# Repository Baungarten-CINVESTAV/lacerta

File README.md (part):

# Lacerta: Open Hardware Interface Engine for Embedded Systems

## Project Overview

**Lacerta** is an open-source hardware platform that enables the rapid creation of graphical interfaces for embedded systems using custom silicon.

**The whole documentation can be found** [**here**](https://baungarten-cinvestav.github.io/lacerta/).

The system allows developers to design graphical interfaces using a graphical configuration tool and deploy them directly to hardware implemented in a custom ASIC integrated with the Caravel SoC platform. The hardware renders the interface in real time and outputs the result to SPI-driven TFT/OLED screens commonly used in embedded devices.

The generated interface may include visual components such as:

- Buttons
- Horizontal and vertical bars
- Numeric indicators
- Status indicators

<p align="center">
<b>Figure 1.</b> Examples of graphical components supported by Lacerta, including buttons, horizontal and vertical bars, numeric indicators, graphics, and status indicators used to visualize real-time system data.
</p>

The ASIC receives information via UART streams and supports two main modes of operation for updating the display:

1. **Direct Mode:** Data received via UART is sent directly to the user project area. In this mode, the values are updated on the SPI TFT/OLED screen with minimal latency, ideal for simple or time-critical updates.

2. **Processing Mode:** Data from UART is first routed to the integrated RISC-V core, where any mathematical operations, functions, or custom logic can be applied. After processing, the results are sent to the user project area to update the display. This mode is suitable for applications requiring data manipulation or more complex interface logic.

This flexible architecture allows Lacerta to efficiently manage multiple inputs and screen objects using a single UART protocol, adapting to both straightforward and advanced use cases. Any other signal types must be converted to UART beforehand by external interface circuitry or preprocessing devices.

<p align="center">
<b>Figure 2.</b> Lacerta system concept: signals are processed by the Lacerta ASIC to generate the custom graphical HMI displayed on SPI-driven TFT/OLED displays for compact embedded installations.
</p>

# System Architecture Summary

The Lacerta platform is an open-source embedded graphics system built from four main parts: custom silicon, board-level hardware, firmware/control logic, and interface software. Together, these layers allow a host system to load graphics data, update interface objects, and drive a small SPI-connected display efficiently.

## Core architecture

Lacerta platform is a custom ASIC implemented in the **SKY130 process** and integrated inside the **Caravel user project area**. This subsystem realizes the hardware graphics engine that receives interface commands, updates the internal display state, and generates the output stream presented on the display.

The Lacerta ASIC follows a memory-centric architecture. Configuration data and runtime values enter the system through **UART**. Depending on the selected operating mode, the received data can be forwarded directly to the user project area or first processed by the embedded **Caravel RISC-V** processor. Internal transactions are routed through the **Wishbone interconnect** to the rendering logic, which updates the frame contents stored in memory. The display output block then reads that memory and continuously converts it into the signal required by the connected **SPI TFT/OLED display**.

The ASIC includes the following main modules:

- the external SRAM interface,
- the TFT SPI interface,
- the UART command interface,
- the Wishbone interface,
- the screen update logic,
- the drawing logic,
- and the shared memory subsystem.

<p align="center">
<b>Figure 3.</b> Block diagram of the Lacerta ASIC inside the Caravel environment. The figure shows how UART data and the embedded Caravel RISC-V processor interact through the Wishbone-connected control path, rendering logic, and memory subsystem; the updated frame data is then read by the display output block to drive the screen.
</p>

## Main subsystems

### Memory subsystem

The memory subsystem manages buffered access to external SRAM. It uses FIFOs, read/write buffering, and arbitration logic so several blocks can share memory safely without needing to handle low-level SRAM timing directly.

### Screen output subsystem

The screen path reads pixel data from memory and converts it into SPI transactions for the display. It supports TFT initialization, full or partial region refreshes, and a color lookup mechanism that maps compact pixel codes to RGB565 values. This reduces memory usage and makes repeated HMI colors efficient to store.

### Drawing subsystem

The drawing logic updates only the parts of the image that change. The `mask_generator` reads current pixel data, modifies selected regions based on object type, writes the result back to SRAM, and then triggers a refresh of the affected rectangle. This makes the system well suited for HMI elements such as bars, graphs, booleans, and segmented displays.

### Command and control subsystem

The control path is coordinated by `command_arbiter_decoder`, which receives transactions from UART and Wishbone interfaces and turns them into actions such as memory access, object redraws, screen refreshes, color-table updates, and reset/control operations.

### UART and Wishbone interfaces

UART provides an external host-facing command port for loading assets, configuring the display, and triggering updates. Wishbone provides processor-oriented access to both control registers and shared memory, allowing the embedded Caravel processor or another SoC master to work with the same graphics system.

## Typical operation

In normal use, a host first loads graphics assets or configuration data into SRAM. The display is initialized, then object updates are triggered through UART or processor commands. The drawing engine modifies only the required image region in memory, and the screen subsystem refreshes only that changed rectangle on the TFT. This avoids full-screen redraws and improves efficiency for dynamic interfaces.

## Lacerta board role

The Lacerta Board packages the SoC with the supporting hardware needed for practical use, including power regulation, clocking, USB-to-serial connectivity, SPI Flash support, GPIO access, and display/peripheral connections. It serves as the physical platform for development, testing, and demonstration of the Lacerta graphics architecture.

# System Development

The development of the Lacerta platform spans the complete hardware and software realization flow, from digital design and verification to physical implementation and system-level integration. This section describes the main stages used to transform the Lacerta concept into a functional platform, including RTL design, verification, layout generation, gate-level validation, PCB development, and the creation of the interface design software.

Together, these activities define the engineering workflow followed to implement, test, and deploy Lacerta as an open-source embedded graphical interface system. Each subsection highlights a different part of this process and explains how the individual development tasks contribute to the final platform.

## Lacerta RTL

**RTL code can be found** [**here**](https://github.com/Baungarten-CINVESTAV/lacerta/tree/main/verilog/rtl).

### System Purpose

The system is designed to display graphical HMI content on a TFT screen and to update only the screen regions that change.

At a functional level, the system must:

- receive commands and image-related data,
- store image bytes and mask bytes in external SRAM,
- modify selected objects inside the stored image,
- fetch the corresponding pixel data,
- convert logical pixel information into display colors,
- and transmit the final bytes to the TFT controller.

The design is organized around a shared memory architecture. Instead of each module touching the SRAM directly, all active clients use a common memory subsystem with buffered read and write channels, as shown in the figure below.

### High-Level Functional Flow

The complete display flow is:

1. A host or processor sends control commands or image data.
2. The command path decodes the request and either:
   - writes data into the shared memory system,
   - updates display-related configuration,
   - or starts a drawing operation.
3. The memory subsystem transfers bytes between internal buffers and external SRAM.
4. If an HMI object changes, `mask_generator` reads the corresponding image region, updates the stored bytes, and writes the modified data back into SRAM.
5. Once the image region is ready, `screen_system` requests the affected window from memory.
6. `tft_control_fsm` streams TFT commands and pixel bytes through `spi_master`.
7. The TFT receives only the updated region instead of a full-screen redraw.

This makes the system well suited for dashboards, indicators, bars, graphs, and symbolic objects that change frequently in small areas.

### Top-Level Integration (User Project Wrapper)

#### `dig_top.v` 

`dig_top` is the main integration point of the RTL system.
It connects:
- the UART interface,
- the Wishbone interface,
- the external SRAM,
- the TFT SPI pins,
- the shared memory subsystem,
- the drawing engine,
- and the display engine.
Its main functional job is to route requests from several clients into the memory system and to coordinate which subsystem is producing or consuming pixel data.

The clients connected to the shared memory system are:

- UART host write path,
- UART host read path,
- screen-system read path,
- drawing-engine read path,
- drawing-engine write path,
- Wishbone memory read path,
- Wishbone memory write path.

Inside `dig_top`, each client is assigned to a dedicated buffer slot. The top-level combinational logic packs the individual requests into the vectors expected by `mem_sys`.

`dig_top` also derives the frame-update rectangle used by the display block:

- `frame_st_x`
- `frame_end_x`
- `frame_width`
- `frame_st_y`
- `frame_end_y`
- `frame_height`
- `frame_st_pix`

These values are taken from the drawing object parameters so that, after a drawing operation, the correct screen region can be refreshed automatically.

Another important top-level task is Wishbone routing. `dig_top` chooses whether a Wishbone transaction goes to:

- `wb_slave_memory_mapped` for control/MMIO accesses,
- or `wb_slave_to_mem_sys_ports` for direct SRAM-backed data accesses.

### End-to-End Operation Examples

#### Example 1: Loading image data from UART

1. The host sends UART packets.
2. `uart_ip_memory_mapped` converts them into internal writes.
3. `command_arbiter_decoder` interprets those writes as host memory-transfer commands.
4. The host write buffer receives the data bytes.
5. `mem_sys` schedules the write burst.
6. `buffers_discharger` sends the bytes to SRAM through `sram_controller`.

#### Example 2: Updating an HMI object

1. The host or processor writes object parameters.
2. `command_arbiter_decoder` stores width, height, position, object value, and memory addresses.
3. A start command asserts `drw_inc_start`.
4. `mask_generator` begins a read-modify-write sequence.
5. The old bytes are fetched from SRAM through `mem_sys`.
6. The updated bytes are written back to SRAM through `mem_sys`.
7. `mask_generator` asserts `ss_start`.
8. `screen_system` refreshes the affected rectangle on the TFT.

#### Example 3: Refreshing the sidebar

1. A control write asserts `ss_ld_sidebar`.
2. `tft_control_fsm` programs the sidebar coordinates into the TFT.
3. It requests the corresponding SRAM burst.
4. Two bytes per pixel are read.
5. Those bytes are transmitted directly through `spi_master`.

### Main Functional Role of Each Major Module

- `dig_top`: integrates the whole system and routes all subsystem interfaces.
- `command_arbiter_decoder`: converts UART/Wishbone commands into internal control actions.
- `uart_ip_memory_mapped`: converts UART packets into internal memory-mapped transactions.
- `wb_slave_memory_mapped`: converts Wishbone MMIO accesses into control transactions.
- `wb_slave_to_mem_sys_ports`: converts Wishbone data accesses into shared-memory bursts.
- `mem_sys`: arbitrates shared access to external SRAM.
- `buffers`: stores temporary read and write data for all clients.
- `buffers_filler`: fills read buffers from SRAM.
- `buffers_discharger`: empties write buffers into SRAM.
- `sram_controller`: drives the physical SRAM pins.
- `mask_generator`: updates image regions according to HMI object logic.
- `screen_system`: top display block for TFT output.
- `tft_control_fsm`: performs TFT initialization and region-based pixel transfer.
- `color_mapping_table`: converts compact pixel codes into RGB565 colors.
- `spi_master`: serializes commands and pixel bytes onto the TFT SPI bus.

## Lacerta Verification

**Verilog TB code can be found** [**here**](https://github.com/Baungarten-CINVESTAV/lacerta/tree/main/verilog/dv/lacerta).

A layered verification strategy was used to validate Lacerta from block level up to full-system behavior. The intent was not only to prove that individual modules operate correctly in isolation, but also to verify that the complete command, memory, drawing, and display paths remain coherent when exercised through the same interfaces used in deployment.

At the block level, dedicated environments were created for the UART front end, the shared memory subsystem, the Wishbone adapters, the command decoder, and the display-related logic. These environments focused on local protocol correctness, handshake legality, data stability, and forward progress. The later sections of this document list the principal checks captured for each block.

At the system level, the main integration environment is `verif/dig_top_tb.sv`. This testbench drives the top-level `dig_top` instance through the UART path, connects the design to an SRAM behavioral model (`CY7C1049GN_i`), and observes the TFT SPI outputs exactly as a real deployment would use them. In practice, this makes the testbench an end-to-end verification vehicle: a command is injected as UART traffic, decoded by the control plane, executed through the memory subsystem, and finally checked either at the SRAM image or at the TFT serial output.

<p align="center">
<b>Figure 4.</b> The diagram summarizes the main verification components, including the clock and reset infrastructure, golden reference data, stimulus path, UART bus functional model, SRAM model, and checker logic used to validate the DUT behavior during gate-level simulation.
</p>

More information about the simulation flow, active checkers, and expected data paths can be found in [dig_top_tb_flow_diagram.html](dig_top_tb_flow_diagram.html).

### System-Level Verification

The full-system verification flow is organized around three complementary ideas:

1. **Interface-faithful stimulus**  
   The testbench does not force deep internal signals to mimic system behavior. Instead, it uses the UART Bus Functional Model (`uart_bfm`) and the helper task `uart_write_mem()` to generate valid command packets byte by byte. This ensures that the UART receive path, packet decoder, command arbiter, and downstream blocks are exercised together.

2. **Independent reference data**  
   The testbench builds its own expected data structures before execution begins:
    `tft_init_mem` stores the expected TFT initialization sequence, including command, data, and delay entries.
    `tft_sidebar` stores the expected sidebar stream sent to the TFT.
    `tft_active_area` stores the logical active-screen image used for full-frame display verification.
    `tb_sram` acts as a golden SRAM image. It is initialized from the active-area data and then updated by the testbench's own object-drawing rules before being compared against the DUT-visible SRAM model.

3. **Concurrent checking**  
   Verification is not deferred to a single final comparison. The testbench runs several checker threads in parallel, so protocol violations, timing mismatches, stream ordering errors, and memory corruption are detected close to the cycle where they occur. This is especially important for gate-level simulation, where failures may arise from control sequencing or handshake timing rather than purely functional logic.

### `dig_top_tb.sv` Verification Flow

The top-level testbench starts from a simple but realistic infrastructure:

- a 50 MHz clock generated with `always #10ns clk = !clk;`,
- an active-low reset released after 40 ns,
- an SRAM behavioral model connected to the external-memory pins,
- UART-driven stimulus,
- a serial-output checker for the TFT SPI path,
- and a 30-second timeout thread to convert deadlock into an explicit failure.

After reset, the system verification scenario progresses through the following phases.

#### 1. TFT initialization memory programming

The testbench writes every entry of `tft_init_mem` through UART to the control address used by the screen subsystem. This stage verifies that Lacerta accepts configuration traffic through the host path and correctly stores screen-initialization data before any display action is requested.

#### 2. TFT initialization sequence execution

Once the initialization table is loaded, the testbench configures the SPI clock divider and triggers screen initialization. A dedicated checker thread waits until the TFT control FSM enters its initialization state and then validates each emitted entry:

- for command/data entries, the checker compares `{rom_type, tnsm_data}` against the expected `tft_init_mem` content;
- for delay entries, it measures the elapsed clock cycles and confirms that the observed delay is at least the programmed number of milliseconds multiplied by `CLK_CYCLES_PER_MS`.

This stage verifies more than register programming. It checks that the initialization ROM is consumed in the correct order, that delay entries are honored in time, and that the SPI path receives the exact bytes expected by the TFT controller. After the sequence completes, the testbench asserts that `initialization_done` is high.

#### 3. Sidebar transfer verification

The testbench then prepares a burst write into the shared memory system and streams the sidebar payload through repeated UART writes. After the sidebar-load command is issued, the testbench checks both control behavior and output behavior:

- `sidebar_ongoing` must assert after the command and later deassert when the transfer completes;
- the read buffer must be empty and the read-page generator must be idle at the end of the operation;
- every SPI byte transmitted during the sidebar update must match the expected `tft_sidebar` sequence;
- the `tft_dc` line must indicate command bytes for `CASET`, `RASET`, and `RAMWR`, and data bytes everywhere else.

This verifies the complete path from host programming, to SRAM write buffering, to screen-system memory fetch, to TFT serialization.

#### 4. Color-mapping table programming

The testbench writes randomized RGB565 values into every color-map entry and then reads the corresponding internal table state after a short propagation delay. This confirms that compact logical pixel codes used in the screen image are translated through the correct table entries before being sent to the TFT interface.

#### 5. Full active-screen fetch and display

To verify full-image display behavior, the testbench first loads the active-screen image into SRAM through the UART-controlled write path. It then programs object geometry fields so the screen subsystem fetches the entire active display region and emits it over SPI.

During this phase, the verification logic checks:

- that the TFT control FSM asserts `busy` after the fetch request and later returns to idle;
- that the read buffer is empty and the page generator is no longer busy after completion;
- that the command/window bytes (`CASET`, `RASET`, `RAMWR`, and coordinate bytes) match the expected `tft_active_area` header;
- that each logical pixel in `tft_active_area` is converted into the correct two-byte RGB565 value using the live `color_map` table;
- and that the command/data framing on `tft_dc` remains correct during the whole transfer.

This is an important system-level check because it validates the interaction among stored pixel data, color expansion, frame-window generation, TFT command sequencing, and SPI serialization.

#### 6. Constrained-random drawing-object verification

After the static display paths are verified, the testbench executes `TB_NUM_OBJECTS` randomized drawing scenarios. For each iteration it selects:

- an object type,
- object width and height,
- a value parameter,
- a legal start position (`st_x`, `st_y`),
- and, for mask objects, a legal mask-source base address.

The object type rotates through the drawing modes implemented in the testbench tasks:

- `draw_horizontal_type()`
- `draw_vertical_type()`
- `draw_graph_type()`
- `draw_mask_type()`

Each task programs the DUT through UART exactly as software would: it writes object type, dimensions, start address, screen coordinates, and trigger/value fields. The testbench then waits for the drawing engine completion handshake (`MASK_GEN_PATH.done`) and updates the shadow image `tb_sram` according to an independent expected-behavior model:

- **Horizontal object:** the MSB of each target pixel is set according to the horizontal position relative to `obj_value`.
- **Vertical object:** the MSB of each target pixel is set according to the vertical position relative to `obj_value`.
- **Graph object:** the existing region is shifted and a new column is inserted, modeling graph-history behavior rather than a simple overwrite.
- **Mask object:** the update uses a second memory region as the mask source, stressing source/destination addressing interactions.

After every object operation, `check_sram_consistency()` compares the golden `tb_sram` contents against the actual external SRAM model seen by the DUT. This immediate comparison is valuable because it localizes failures to the most recent object operation instead of postponing diagnosis to the end of the simulation.

#### 7. Microprocessor-enable handoff

At the end of the scenario, the testbench issues the UART command that enables the embedded microprocessor path and verifies that `up_enable` is asserted. This closes the loop on one more top-level control action and ensures the system can hand control to the processor-side flow after host-side configuration.

### Active Checker Structure

The `dig_top_tb.sv` environment contains several simultaneously active verification mechanisms:

- **TFT initialization checker:** validates initialization bytes and delay lengths.
- **Sidebar stream checker:** validates TFT payload bytes and command/data framing.
- **Active-area stream checker:** validates frame-window commands and RGB565-expanded pixel output.
- **SRAM shadow-model checker:** compares the expected image memory against the SRAM model after each draw operation.
- **SPI serialization checker:** samples `tft_mosi` on `tft_sck` edges and confirms that every acknowledged `tnsm_data` byte is serialized MSB first.
- **Control/status assertions:** check flags such as `initialization_done`, `sidebar_ongoing`, `busy`, buffer-empty conditions, and `up_enable`.
- **Timeout protection:** terminates the simulation with a fatal error if the full scenario fails to make progress within 30 seconds.

Together, these checkers provide both transaction-level and bit-level confidence. A failure can therefore be caught as a bad control transition, a wrong memory update, an incorrect TFT byte, or even a serialization mismatch on the SPI output pin.

### Relation to GLS and Documentation Artifacts

This same end-to-end style is especially useful for gate-level simulation because it exercises long control sequences, back-pressure conditions, and external-interface timing without simplifying the problem to a purely combinational comparison. More detailed information about the simulation flow, active checkers, and expected data paths can be found in [dig_top_tb_flow_diagram.html](dig_top_tb_flow_diagram.html). That file documents the actual structure implemented in `dig_top_tb.sv`: UART-driven initialization, sidebar transfer, color-map programming, full active-area fetch, constrained-random object drawing with per-object SRAM comparison, and final processor enable.

Overall, the Lacerta verification methodology combines block-level protocol checking, system-level end-to-end stimulus, reference-model comparison, and gate-level observability. This gives strong confidence that the platform is not only logically correct, but also integration-ready across its communication, memory, drawing, and display subsystems.

### WB Slave to Memory Mapped

The verification plan for the **WB Slave to Memory Mapped** block focuses on protocol correctness, proper memory-side control generation, and legal read/write handshaking.

1. Verify that the Wishbone slave acknowledges only when a valid master request is active.
2. Verify that an active Wishbone request is acknowledged within the maximum allowed number of clock cycles.
3. Verify that `wb_ack_o` is asserted for only one clock cycle per transaction.
4. Verify that address, data, and control signals remain stable while a request is active and has not yet been acknowledged.
5. Verify that `mem_we` is asserted, and `mem_re` is not asserted, during Wishbone write requests.
6. Verify that `mem_re` is asserted, and `mem_we` is not asserted, during Wishbone read requests.
7. Verify that `wb_cyc_i` and `wb_stb_i` are deasserted only after `wb_ack_o`, preventing overlapping requests.
8. Verify that `mem_waddr`, `mem_wdata`, and `mem_wmask` correctly reflect the Wishbone address, data, and byte-select signals during write requests.
9. Verify that `mem_raddr` correctly reflects the Wishbone address during read requests.
10. Verify that `wb_dat_o` returns the same data received from memory when a Wishbone read request completes.
11. Verify that `mem_wr_data_ack` can be asserted only while a Wishbone write transaction is in progress.
12. Verify that `mem_rdy` can be asserted only while a Wishbone read transaction is in progress.

### WB Slave to Read/Write Ports

The verification plan for the **WB Slave to Read/Write Ports** block checks correct Wishbone behavior, proper coordination with the memory-system ports, and correct sequencing of read and write transactions initiated by the microprocessor side.

1. Verify that the Wishbone slave acknowledges only when a valid master request is active.
2. Verify that `wb_ack_o` is asserted for only one clock cycle per transaction.
3. Verify that address, data, and control signals remain stable while a request is active and has not yet been acknowledged.
4. Verify that `wpg_busy` is asserted only for Wishbone write requests and remains clear for read requests.
5. Verify that `wpg_busy` remains asserted until `wpg_ack` is received.
6. Verify that `rpg_busy` is asserted only for Wishbone read requests and remains clear for write requests.
7. Verify that `rpg_busy` remains asserted until `rpg_ack` is received.
8. Verify that `wb_cyc_i` and `wb_stb_i` are deasserted only after `wb_ack_o`, preventing overlapping requests.
9. Verify that `up_en` does not change while a read or write process is in progress.
10. Verify that `up_soft_reset` does not change while a read or write process is in progress.
11. Verify that `wpg_st_addr`, `wpg_burst_length`, and `wr_buff_wdata` are correctly loaded during Wishbone write requests.
12. Verify that `wpg_st_addr`, `wpg_burst_length`, and `wr_buff_wdata` remain stable until `wpg_ack` is asserted.
13. Verify that `rpg_st_addr` and `rpg_burst_length` are correctly loaded during Wishbone read requests.
14. Verify that `rpg_st_addr` and `rpg_burst_length` remain stable until `rpg_ack` is asserted.
15. Verify that `wr_buff_wren` is asserted only during Wishbone write requests and only once per write transaction.
16. Verify that `rd_buff_rden` is asserted only during Wishbone read requests and exactly `NUM_ACCESSES` times per read transaction.
17. Verify that `rpg_ack` can be asserted only while a master read operation is ongoing.
18. Verify that `wpg_ack` can be asserted only while a master write operation is ongoing.
19. Verify that a Wishbone read transaction completes when `rpg_ack` is asserted.
20. Verify that a Wishbone write transaction completes when `wpg_ack` is asserted.
21. Verify that the read buffer is empty whenever no Wishbone read operation is in progress.
22. Verify that the data returned at the end of a Wishbone read matches the data delivered by the memory system.
23. Verify that Wishbone read and write transactions can start only when the microprocessor interface is enabled and not in soft reset.

### Command Arbiter Decoder

The verification plan for the **Command Arbiter Decoder** block checks the validity of drawing commands, busy-state behavior, and the control rules used when enabling or resetting the memory-access path.

1. Verify that when `drw_inc_start` is asserted, the drawing object type is within the valid range and both object width and object height are greater than `MIN_OBJECT_WIDTH_HEIGHT`.
2. Verify that asserting `drw_inc_start` causes `drw_inc_busy` to transition from `0` to `1`.
3. Verify that the drawing data sent to the rendering circuit remains stable while `drw_inc_busy` is asserted.
4. Verify that `drw_inc_busy` is not asserted for longer than `DRW_BUSY_TIMEOUT` clock cycles.
5. Verify that `wb_slave_up_en` is asserted when the UART write command address is `18`.
6. Verify that `wb_slave_up_en` can be deasserted only when no memory-system access transaction is in progress.
7. Verify that `up_soft_reset` can be asserted only when no memory-system access transaction is in progress.

### Mask Generator

The verification plan for the **Mask Generator** block validates correct start/busy sequencing and ensures that internal read/write activity occurs only while the block is actively processing a drawing operation.

1. Verify that asserting `start` causes `busy` to transition from `0` to `1`.
2. Verify that `start` cannot be asserted while `busy` or `done` is already asserted.
3. Verify that when `busy` is deasserted, `rpg_busy` and `wpg_busy` are both low and `rd_buff_empty` is high.
4. Verify that `rd_buff_rden` cannot be asserted when `rd_buff_empty` is high.
5. Verify that `wr_buff_wren` cannot be asserted when `wr_buff_full` is high.
6. Verify that `rpg_busy`, `wpg_busy`, `rpg_ack`, `wpg_ack`, `wr_buff_full`, `rd_buff_rden`, and `wr_buff_wren` can be asserted only while `busy` is high.

## Lacerta RTL Verification

**Verilog TB code can be found** [**here**](https://github.com/Baungarten-CINVESTAV/lacerta/tree/main/verilog/dv/lacerta).

The RTL simulation stage was used to verify the functional behavior of the Lacerta top-level design and to confirm the correctness of the TFT initialization transaction sequence before physical implementation. In this test, the simulation output shows that the expected delays were observed and that the initialization values stored in `tft_init_mem` were transmitted correctly to `spi_master`. The resulting log provides evidence that the initialization FSM and SPI output path behave as intended during the early display bring-up sequence at the RTL verification stage.

A section from the RTL simulation log is shown below. The complete log file is available for download here: [lacerta_gate_level_simulation.log](documentation_mkdoc/docs/lacerta_gate_level_simulation.log).

```text
Time resolution is 1 ps
open_wave_config /home/miguel/Documents/lacerta/verif/work/work.dig_top_tb.wcfg
run -all
delay encountered 20
PASS: correct delay 1020321 for entry 0 was measured
delay encountered 120
PASS: correct delay 6049997 for entry 1 was measured
PASS: correct tft_init_mem data 0001 for entry 2 was sent to spi_master
delay encountered 150
PASS: correct delay 7549959 for entry 3 was measured
PASS: correct tft_init_mem data 0011 for entry 4 was sent to spi_master
delay encountered 120
PASS: correct delay 6049959 for entry 5 was measured
PASS: correct tft_init_mem data 003a for entry 6 was sent to spi_master
PASS: correct tft_init_mem data 0155 for entry 7 was sent to spi_master
delay encountered 10
PASS: correct delay 549920 for entry 8 was measured
PASS: correct tft_init_mem data 0036 for entry 9 was sent to spi_master
PASS: correct tft_init_mem data 01a8 for entry 10 was sent to spi_master
PASS: correct tft_init_mem data 002a for entry 11 was sent to spi_master
PASS: correct tft_init_mem data 0100 for entry 12 was sent to spi_master
PASS: correct tft_init_mem data 0100 for entry 13 was sent to spi_master
PASS: correct tft_init_mem data 0101 for entry 14 was sent to spi_master
PASS: correct tft_init_mem data 013f for entry 15 was sent to spi_master
PASS: correct tft_init_mem data 002b for entry 16 was sent to spi_master
PASS: correct tft_init_mem data 0100 for entry 17 was sent to spi_master
PASS: correct tft_init_mem data 0100 for entry 18 was sent to spi_master
PASS: correct tft_init_mem data 0100 for entry 19 was sent to spi_master
PASS: correct tft_init_mem data 01ef for entry 20 was sent to spi_master
PASS: correct tft_init_mem data 0020 for entry 21 was sent to spi_master
PASS: correct tft_init_mem data 0013 for entry 22 was sent to spi_master
```

### RTL/GL simulation

A custom script was developed to execute RTL and GL simulations with the Caravel infrastructure, as the default Caravel simulation flow was out of date and only supported cocotb-based testbenches. This approach was necessary to correctly run assertion-based testbenches and ensure compatibility with the current Lacerta verification environment, which relies on SystemVerilog assertions and traditional testbench flows.

The custom script, located in the [`dv_setup`](dv_setup) directory (`lacerta/dv_setup`), automates the setup and execution of both RTL and gate-level (GL) simulations. It handles environment configuration, Makefile patching, and the selection of the appropriate simulation mode (`SIM_MODE=RTL` or `SIM_MODE=GL`). The script also allows users to select which DV test to run via the `DV_TEST` variable, making it flexible for different verification scenarios.

This approach ensures that all assertions and checkers in the testbenches are properly evaluated during simulation, which is not possible with the default Caravel cocotb-only flow. The script supports both host-based and Docker-based simulation environments, making it suitable for a variety of development setups.

The main testbench (`lacerta_tb.sv`) and its associated waveform files can be found in the `lacerta/verilog/dv/lacerta` folder. The following figure shows an example waveform generated during simulation:

<p align="center">
<b>Figure 6.</b> Example simulation waveform from the Lacerta RTL testbench, illustrating the verification an initial configuration of the memory_system through UART using IO port 5 an 6.
</p>

For detailed instructions on how to use the RTL/GL simulation flow, refer to the documentation and scripts in

## Hardening Configuration

**Librelane configuration can be found** [**here**](https://github.com/Baungarten-CINVESTAV/lacerta/tree/main/openlane/user_project_wrapper).

This page documents the OpenLane hardening setup used for the `user_project_wrapper` flow in Lacerta and records the top-level hardening option selected for the project.

### Selected Hardening Option

The selected hardening option is:

**Flat on Top-Level (Single Flat Design)**

In this approach, the full user project is hardened directly at the `user_project_wrapper` level. OpenLane reads the top-level wrapper together with the project RTL and generates a single physical implementation for the wrapper.

This option is typically used when:

- the goal is to optimize the complete design as one integrated block,
- higher top-level performance is preferred over separate block-level optimization,
- and global placement and routing decisions are acceptable across the full design.

For this flow, the top-level OpenLane run is performed inside:

`openlane/user_project_wrapper`

### Single OpenLane Run Setup

For a flat top-level hardening flow, the wrapper configuration should:

- set `DESIGN_IS_CORE` to `1` when required by the selected OpenLane flow,
- include `user_project_wrapper.v` together with the full user RTL in `VERILOG_FILES`,
- and ensure that `user_project_wrapper.v` directly instantiates the project design.

In Lacerta, the wrapper configuration includes the top-level RTL together with the main functional blocks such as:

- `dig_top.v`
- `command_arbiter_decoder.v`
- UART modules
- Wishbone slave modules
- screen control modules
- drawing modules
- memory-system RTL

### Current Wrapper Configuration

The wrapper hardening file is:

`openlane/user_project_wrapper/config.json`

This configuration includes the full RTL list under `VERILOG_FILES`, which matches the flat top-level hardening strategy. The file also enables several implementation and signoff-related options for a full wrapper run.

Key settings from `config.json`:

```json
"SYNTH_ELABORATE_ONLY": false,
"RUN_POST_GPL_DESIGN_REPAIR": true,
"RUN_POST_CTS_RESIZER_TIMING": true,
"DESIGN_REPAIR_BUFFER_INPUT_PORTS": true,
"FP_PDN_ENABLE_RAILS": true,
"RUN_ANTENNA_REPAIR": true,
"RUN_FILL_INSERTION": true,
"RUN_TAP_ENDCAP_INSERTION": true,
"RUN_CTS": true,
"RUN_IRDROP_REPORT": true
```

Additional implementation-oriented settings used in the same file include:

```json
"SYNTH_STRATEGY": "DELAY 4",
"FP_CORE_UTIL": 30,
"DESIGN_REPAIR_REMOVE_BUFFERS": true,
"DESIGN_REPAIR_MAX_CAP_PCT": 85,
"DESIGN_REPAIR_MAX_SLEW_PCT": 85,
"RUN_POST_GRT_DESIGN_REPAIR": true,
"RUN_POST_GRT_RESIZER_TIMING": true,
"PL_RESIZER_HOLD_SLACK_MARGIN": 0.3,
"GRT_RESIZER_HOLD_SLACK_MARGIN": 0.3
```

### Reference Hardening Variables for Top-Level Integration

The following variables were identified as the hardening option reference for top-level integration:

```json
"QUIT_ON_SYNTH_CHECKS": 1,
"FP_PDN_CHECK_NODES": 1,
"SYNTH_ELABORATE_ONLY": 0,
"PL_RANDOM_GLB_PLACEMENT": 0,
"PL_RESIZER_DESIGN_OPTIMIZATIONS": 1,
"PL_RESIZER_TIMING_OPTIMIZATIONS": 1,
"GLB_RESIZER_DESIGN_OPTIMIZATIONS": 1,
"GLB_RESIZER_TIMING_OPTIMIZATIONS": 1,
"PL_RESIZER_BUFFER_INPUT_PORTS": 1,
"FP_PDN_ENABLE_RAILS": 1,
"GRT_REPAIR_ANTENNAS": 1,
"RUN_FILL_INSERTION": 1,
"RUN_TAP_DECAP_INSERTION": 1,
"RUN_CTS": 1,
"RUN_CVC": 1
```

These settings describe the intended behavior of a robust full-wrapper hardening run, including synthesis checking, placement control, timing optimization, PDN generation, antenna repair, filler insertion, tap/decap insertion, clock-tree synthesis, and final electrical checks.

<p align="center">
<b>Figure 5.</b> KLayout view of the Lacerta custom ASIC layout, showing the physical implementation of the design within the SKY130 Caravel user project area.
</p>

To complement the layout view, Table 1 summarizes the main implementation metrics of the Lacerta chip extracted from the final OpenLane hardening results. These values provide a compact overview of the physical size, logic complexity, utilization, power, timing, and routing quality achieved for the final ASIC integration.

| Parameter                        | Value                        |
|-----------------------------------|------------------------------|
| Technology / integration platform | SKY130 in Caravel user project area |
| Die size                         | 2920 um x 3520 um            |
| Die area                         | 10.2784 mm²                  |
| Core size                        | 2908.58 um x 3497.92 um      |
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
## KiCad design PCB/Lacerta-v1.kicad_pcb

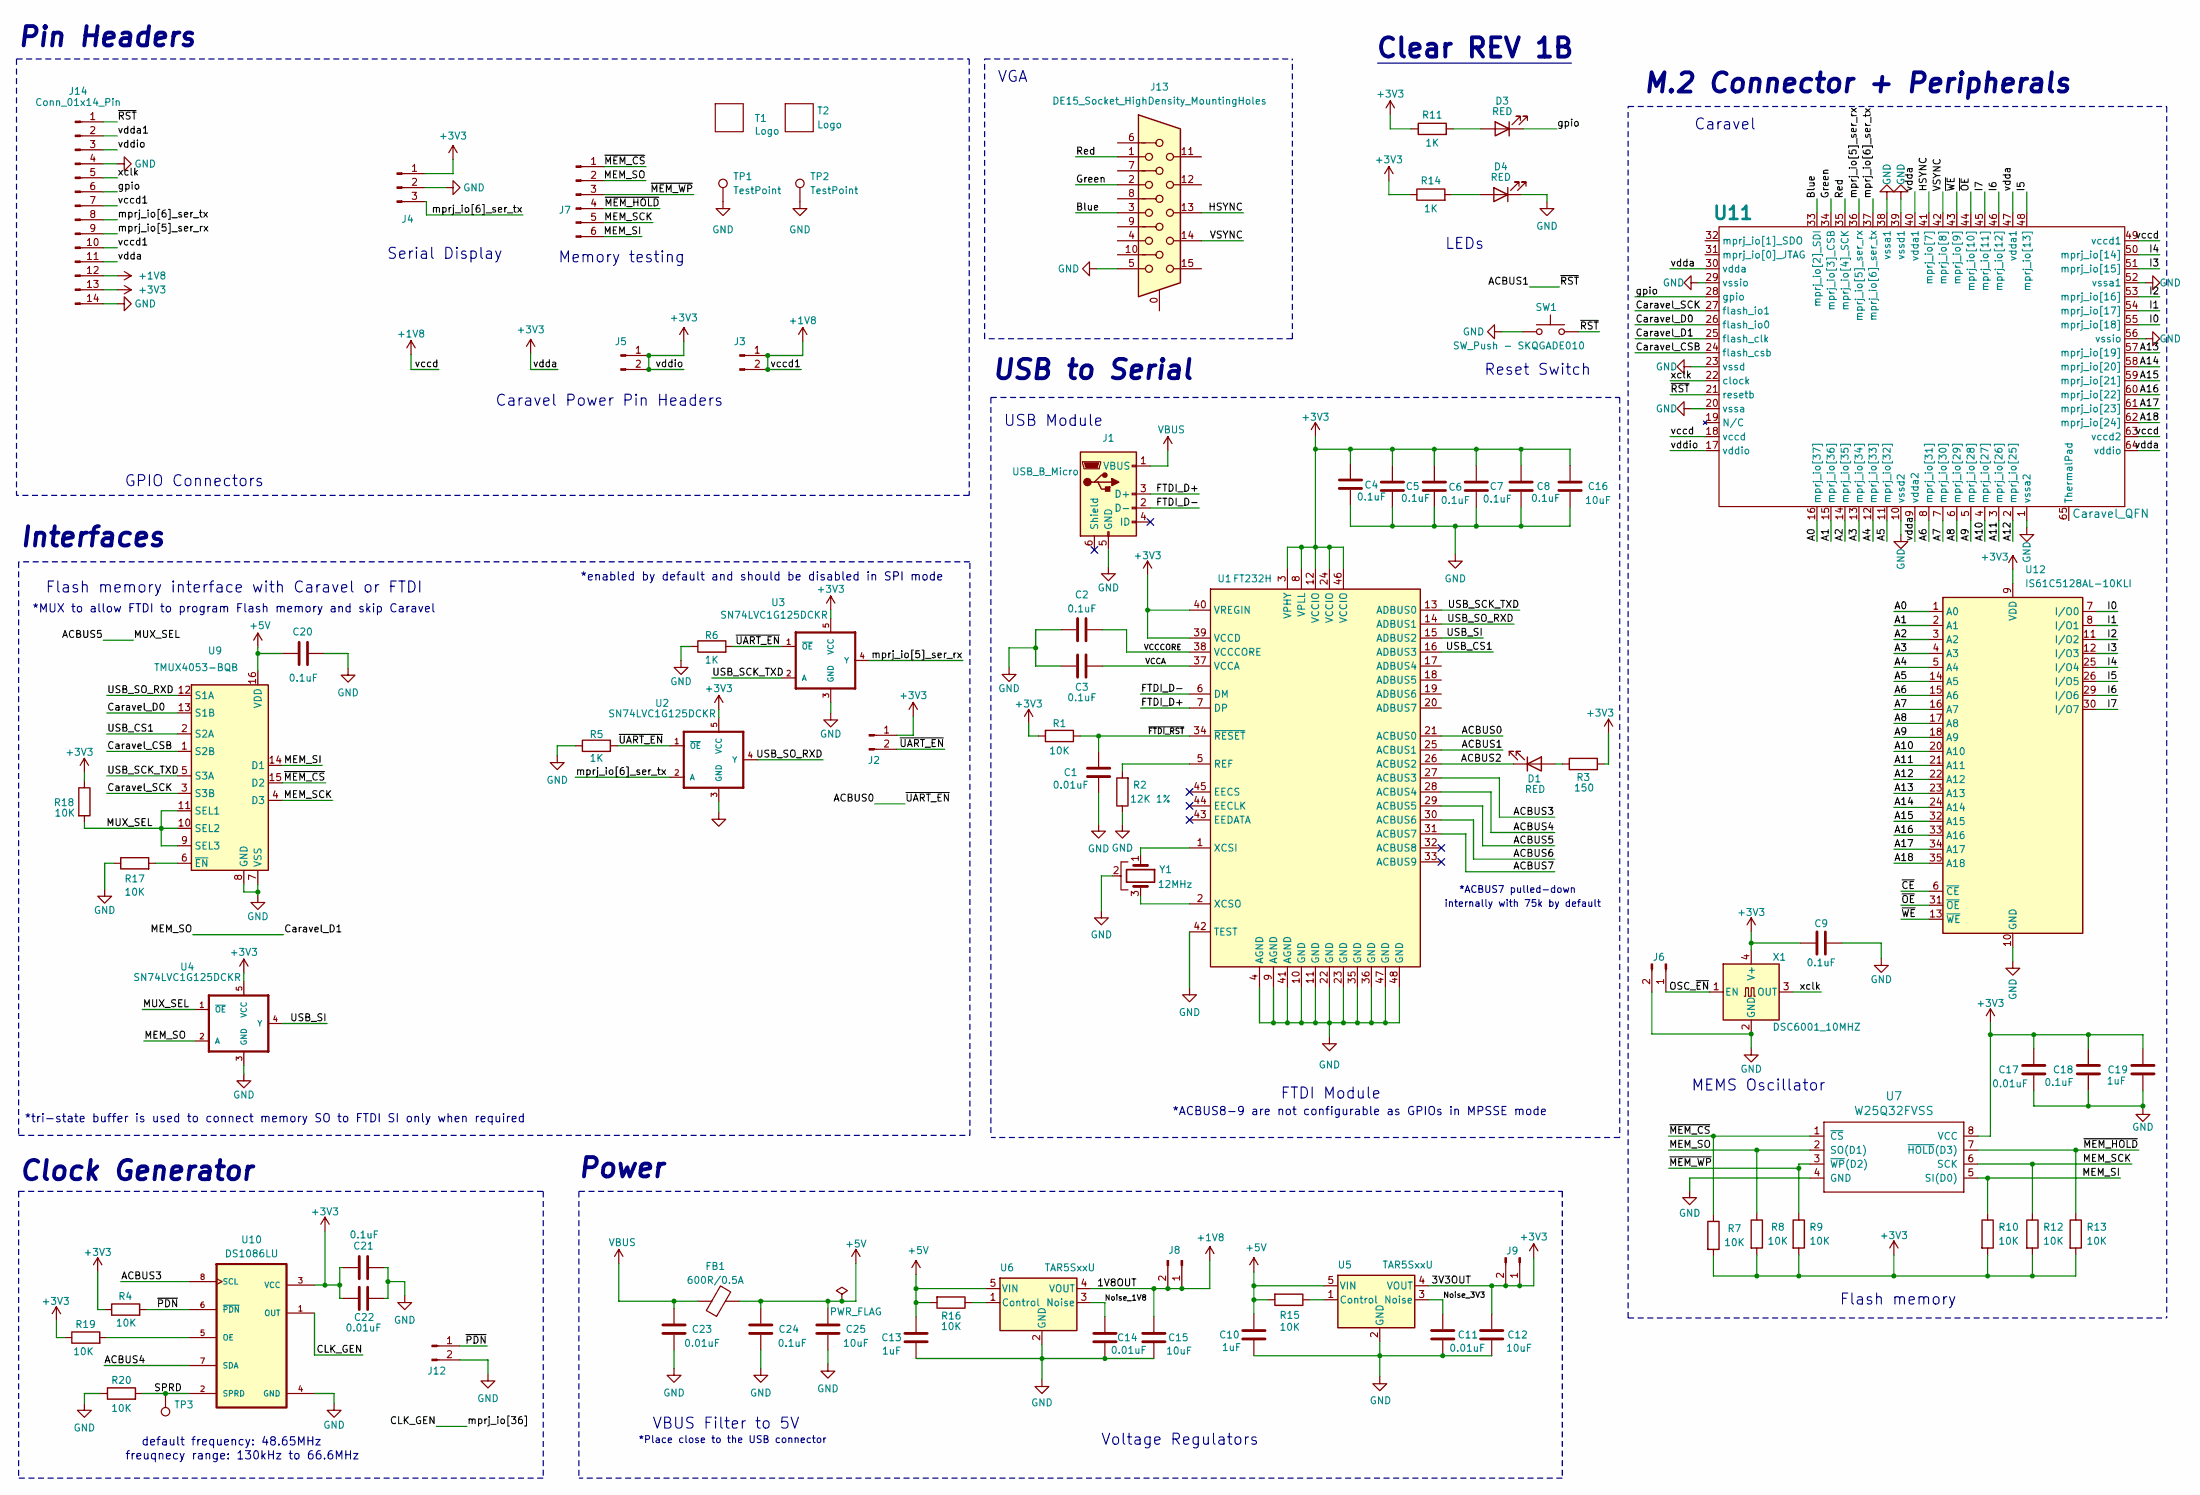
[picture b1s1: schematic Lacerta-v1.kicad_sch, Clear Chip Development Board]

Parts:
C1, C11, C14, C17, C22, C23: 0.01uF; C_0805_2012Metric; Part # C0805C103K5RAC7411
C2, C3, C4, C5, C6, C7, C8, C9, C18, C20, C21, C24: 0.1uF; C_0805_2012Metric; Part # C0805C104K5RAC7411
C10, C13, C19: 1uF; C_0805_2012Metric; Part # 885012207103
C12, C15, C16, C25: 10uF; C_0805_2012Metric; Part # CL21B106KAYQNNE
D1, D3, D4: RED; LED_1206_3216Metric; Part # LTST-C230KRKT
FB1: 600R/0.5A; L_0805_2012Metric; Part # 7427920415
J1: USB_B_Micro; FCI_10118193-0001LF; Part # 10118193-0001LF
J2, J6, J12: Conn_01x02_Pin; PinHeader_1x02_P2.54mm_Vertical
J3, J5, J8, J9: Conn_01x02_Pin; Shorted_PinHeader_1x02_P2.54mm_Vertical
J4: Conn_01x03_Pin; PinHeader_1x03_P2.54mm_Vertical
J7: Conn_01x06_Pin; PinHeader_1x06_P2.54mm_Vertical
J13: DE15_Socket_HighDensity_MountingHoles; DSUB-15-HD_Socket_Horizontal_P2.29x2.54mm_EdgePinOffset8.35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
J14: Conn_01x14_Pin; PinHeader_1x14_P2.54mm_Vertical
R1, R4, R7, R8, R9, R10, R12, R13, R15, R16, R17, R18, R19, R20: 10K; R_0805_2012Metric; Part # RC0805FR-0710KL
R2: 12K 1%; R_0805_2012Metric; Part # RMCF0805FT12K0
R3: 150; R_0805_2012Metric; Part # RNCP0805FTD150R
R5, R6, R11, R14: 1K; R_0805_2012Metric; Part # RC0805FR-071KL
SW1: SW_Push - SKQGADE010; SW4-SMD-5.2X5.2X1.5MM
T1: Logo; logo
T2: Logo; ef_logo
TP1, TP2: TestPoint; TestPoint_Bridge_Pitch2.54mm_Drill1.0mm
TP3: TestPoint; TestPoint_THTPad_2.0x2.0mm_Drill1.0mm
U1: FT232H; QFN-48-1EP_8x8mm_P0.5mm_EP6.2x6.2mm; Part # FT232H
U2, U3, U4: SN74LVC1G125DCKR; SOT65P210X110-5N; Part # SN74LVC1G125DCKR
U5: TAR5SxxU; SOT-353F; Part # TAR5S33UTE85LF
U6: TAR5SxxU; SOT-353F; Part # TAR5S18U-TE85L-F
U7: W25Q32FVSS; SOIC127P790X216-8N; Part # W25Q32JVSSIQ
U9: TMUX4053-BQB; WQFN-16-1EP_2.5x3.5mm_P0.5mm_EP1x2mm; Part # TMUX4053BQBR
U10: DS1086LU; SOP65P490X110-8N; Part # DS1086LU+T
U11: Caravel_QFN; QFN-64-1EP_9x9mm_P0.5mm_EP7.65x7.65mm
U12: IS61C5128AL-10KLI; SOJ-36_10.16x23.495mm_P1.27mm
X1: DSC6001_10MHZ; DSC6001JE1A-010.0000; Part # DSC6001JI1B
Y1: 12MHz; CSTNE12M0GH5L000R0; Part # CSTNE12M0GH5L000R0

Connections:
+1V8: C15.2, J3.1, J3.2, J8.1, J8.2, J14.7, J14.10, J14.12, U6.4 (VOUT), U11.18 (vccd), U11.49 (vccd1), U11.63 (vccd2)
+3V3: C4.2, C5.2, C6.2, C7.2, C8.2, C9.2, C12.2, C16.1, C17.2, C18.1, C19.1, C21.2, C22.2, J2.1, J4.1, J5.1, J5.2, J9.1, J9.2, J14.3, J14.11, J14.13, R1.2, R3.2, R4.1, R7.2, R8.2, R9.2, R10.2, R11.1, R12.2, R13.2, R14.1, R18.1, R19.1, U1.3 (VPHY), U1.8 (VPLL), U1.12 (VCCIO), U1.24 (VCCIO), U1.39 (VCCD), U1.40 (VREGIN), U1.46 (VCCIO), U2.5 (VCC), U3.5 (VCC), U4.5 (VCC), U5.4 (VOUT), U7.8 (VCC), U10.3 (VCC), U11.9 (vdda2), U11.17 (vddio), U11.30 (vdda), U11.40 (vdda1), U11.47 (vdda1), U11.64 (vddio), U12.9 (VDD), U12.27 (VDD), X1.4 (V+)
+5V: C10.2, C13.2, C20.2, C24.2, C25.2, FB1.2, R15.2, R16.2, U5.5 (VIN), U6.5 (VIN), U9.16 (VDD)
/A0: U11.16 (mprj_io[37]), U12.1 (A0)
/A1: U11.15 (mprj_io[36]), U12.2 (A1)
/A2: U11.14 (mprj_io[35]), U12.3 (A2)
/A3: U11.13 (mprj_io[34]), U12.4 (A3)
/A4: U11.12 (mprj_io[33]), U12.5 (A4)
/A5: U11.11 (mprj_io[32]), U12.14 (A5)
/A6: U11.8 (mprj_io[31]), U12.15 (A6)
/A7: U11.7 (mprj_io[30]), U12.16 (A7)
/A8: U11.6 (mprj_io[29]), U12.17 (A8)
/A9: U11.5 (mprj_io[28]), U12.18 (A9)
/A10: U11.4 (mprj_io[27]), U12.20 (A10)
/A11: U11.3 (mprj_io[26]), U12.21 (A11)
/A12: U11.2 (mprj_io[25]), U12.22 (A12)
/A13: U11.57 (mprj_io[19]), U12.23 (A13)
/A14: U11.58 (mprj_io[20]), U12.24 (A14)
/A15: U11.59 (mprj_io[21]), U12.32 (A15)
/A16: U11.60 (mprj_io[22]), U12.33 (A16)
/A17: U11.61 (mprj_io[23]), U12.34 (A17)
/A18: U11.62 (mprj_io[24]), U12.35 (A18)
/ACBUS0: J2.2, R5.2, R6.2, U1.21 (ACBUS0), U2.1 (~OE), U3.1 (~OE)
/ACBUS1: J14.1, SW1.1, U1.25 (ACBUS1), U11.21 (resetb)
/ACBUS2: D1.1 (K), U1.26 (ACBUS2)
/ACBUS3: U1.27 (ACBUS3), U10.8 (SCL)
/ACBUS4: U1.28 (ACBUS4), U10.7 (SDA)
/ACBUS5: R18.2, U1.29 (ACBUS5), U4.1 (~OE), U9.9 (SEL3), U9.10 (SEL2), U9.11 (SEL1)
/ACBUS6: U1.30 (ACBUS6)
/ACBUS7: U1.31 (ACBUS7)
/Blue: J13.3, U11.33 (mprj_io[2]_SDI)
/CLK_GEN: U10.1 (OUT)
/Caravel_CSB: U9.1 (S2B), U11.24 (flash_csb)
/Caravel_D0: U9.13 (S1B), U11.26 (flash_io0)
/Caravel_D1: J7.2, R8.1, U4.2 (A), U7.2 (SO(D1)), U11.25 (flash_clk)
/Caravel_SCK: U9.3 (S3B), U11.27 (flash_io1)
/FTDI_D+: J1.3 (D+), U1.7 (DP)
/FTDI_D-: J1.2 (D-), U1.6 (DM)
/Green: J13.2, U11.34 (mprj_io[3]_CSB)
/HSYNC: J13.13, U11.41 (mprj_io[7])
/I0: U11.55 (mprj_io[18]), U12.7 (I/O0)
/I1: U11.54 (mprj_io[17]), U12.8 (I/O1)
/I2: U11.53 (mprj_io[16]), U12.11 (I/O2)
/I3: U11.51 (mprj_io[15]), U12.12 (I/O3)
/I4: U11.50 (mprj_io[14]), U12.25 (I/O4)
/I5: U11.48 (mprj_io[13]), U12.26 (I/O5)
/I6: U11.46 (mprj_io[12]), U12.29 (I/O6)
/I7: U11.45 (mprj_io[11]), U12.30 (I/O7)
/MEM_SCK: J7.5, R12.1, U7.6 (SCK), U9.4 (D3)
/MEM_SI: J7.6, R10.1, U7.5 (SI(D0)), U9.14 (D1)
/Noise_1V8: C14.1, U6.3 (Noise)
/Noise_3V3: C11.1, U5.3 (Noise)
/OSC_~EN: J6.1, X1.1 (EN)
/Red: J13.1, U11.35 (mprj_io[4]_SCK)
/SPRD: R20.2, TP3.1, U10.2 (SPRD)
/USB_CS1: U1.16 (ADBUS3), U9.2 (S2A)
/USB_SCK_TXD: U1.13 (ADBUS0), U3.2 (A), U9.5 (S3A)
/USB_SI: U1.15 (ADBUS2), U4.4 (Y)
/USB_SO_RXD: U1.14 (ADBUS1), U2.4 (Y), U9.12 (S1A)
/VCCA: C3.2, U1.37 (VCCA)
/VCCCORE: C2.2, U1.38 (VCCCORE)
/VSYNC: J13.14, U11.42 (mprj_io[8])
/gpio: D3.1 (K), J14.6, U11.28 (gpio)
/mprj_io[5]_ser_rx: J14.9, U3.4 (Y), U11.36 (mprj_io[5]_ser_rx)
/mprj_io[6]_ser_tx: J4.3, J14.8, U2.2 (A), U11.37 (mprj_io[6]_ser_tx)
/vdda1: J14.2
/xclk: J14.5, U11.22 (clock), X1.3 (OUT)
/~CE: U12.6 (~CE)
/~FTDI_RST: C1.2, R1.1, U1.34 (~RESET)
/~MEM_CS: J7.1, R7.1, U7.1 (~CS), U9.15 (D2)
/~MEM_HOLD: J7.4, R13.1, U7.7 (~HOLD(D3))
/~MEM_WP: J7.3, R9.1, U7.3 (~WP(D2))
/~OE: U11.44 (mprj_io[10]), U12.31 (~OE)
/~PDN: J12.1, R4.2, U10.6 (~PDN)
/~WE: U11.43 (mprj_io[9]), U12.13 (~WE)
GND: C1.1, C2.1, C3.1, C4.1, C5.1, C6.1, C7.1, C8.1, C9.1, C10.1, C11.2, C12.1, C13.1, C14.2, C15.1, C16.2, C17.1, C18.2, C19.2, C20.1, C21.1, C22.1, C23.2, C24.1, C25.1, D4.1 (K), J1.5 (GND), J4.2, J6.2, J12.2, J13.5, J14.4, J14.14, R2.1, R5.1, R6.1, R17.1, R20.1, SW1.2, TP1.1, TP2.1, U1.4 (AGND), U1.9 (AGND), U1.10 (GND), U1.11 (GND), U1.22 (GND), U1.23 (GND), U1.35 (GND), U1.36 (GND), U1.41 (AGND), U1.42 (TEST), U1.47 (GND), U1.48 (GND), U2.3 (GND), U3.3 (GND), U4.3 (GND), U5.2 (GND), U6.2 (GND), U7.4 (GND), U9.7 (VSS), U9.8 (GND), U10.4 (GND), U11.1 (vssa2), U11.10 (vssd2), U11.20 (vssa), U11.23 (vssd), U11.29 (vssio), U11.38 (vssa1), U11.39 (vssd1), U11.52 (vssa1), U11.56 (vssio), U12.10 (GND), U12.28 (GND), X1.2 (GND), Y1.2
unnamed: D1.2 (A), R3.1
unnamed: D3.2 (A), R11.2
unnamed: D4.2 (A), R14.2
unnamed: R2.2, U1.5 (REF)
unnamed: U1.1 (XCSI), Y1.1
unnamed: U1.2 (XCSO), Y1.3
unnamed: R15.1, U5.1 (Control)
unnamed: R16.1, U6.1 (Control)
unnamed: R17.2, U9.6 (~EN)
unnamed: R19.2, U10.5 (OE)
VBUS: C23.1, FB1.1, J1.1 (VBUS)

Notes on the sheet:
USB to Serial
USB Module
MEMS Oscillator
*Place close to the USB connector
Flash memory interface with Caravel or FTDI
Caravel Power Pin Headers
GPIO Connectors
LEDs
VGA
Flash memory
Serial Display
*MUX to allow FTDI to program Flash memory and skip Caravel
M.2 Connector + Peripherals
*enabled by default and should be disabled in SPI mode
Power
default frequency: 48.65MHz
Pin Headers
VBUS Filter to 5V
Interfaces
Clock Generator
Voltage Regulators
Clear REV 1B
*ACBUS8-9 are not configurable as GPIOs in MPSSE mode
Reset Switch
Memory testing
*ACBUS7 pulled-down
freuqnecy range: 130kHz to 66.6MHz
*tri-state buffer is used to connect memory SO to FTDI SI only when required
internally with 75k by default
FTDI Module
Caravel

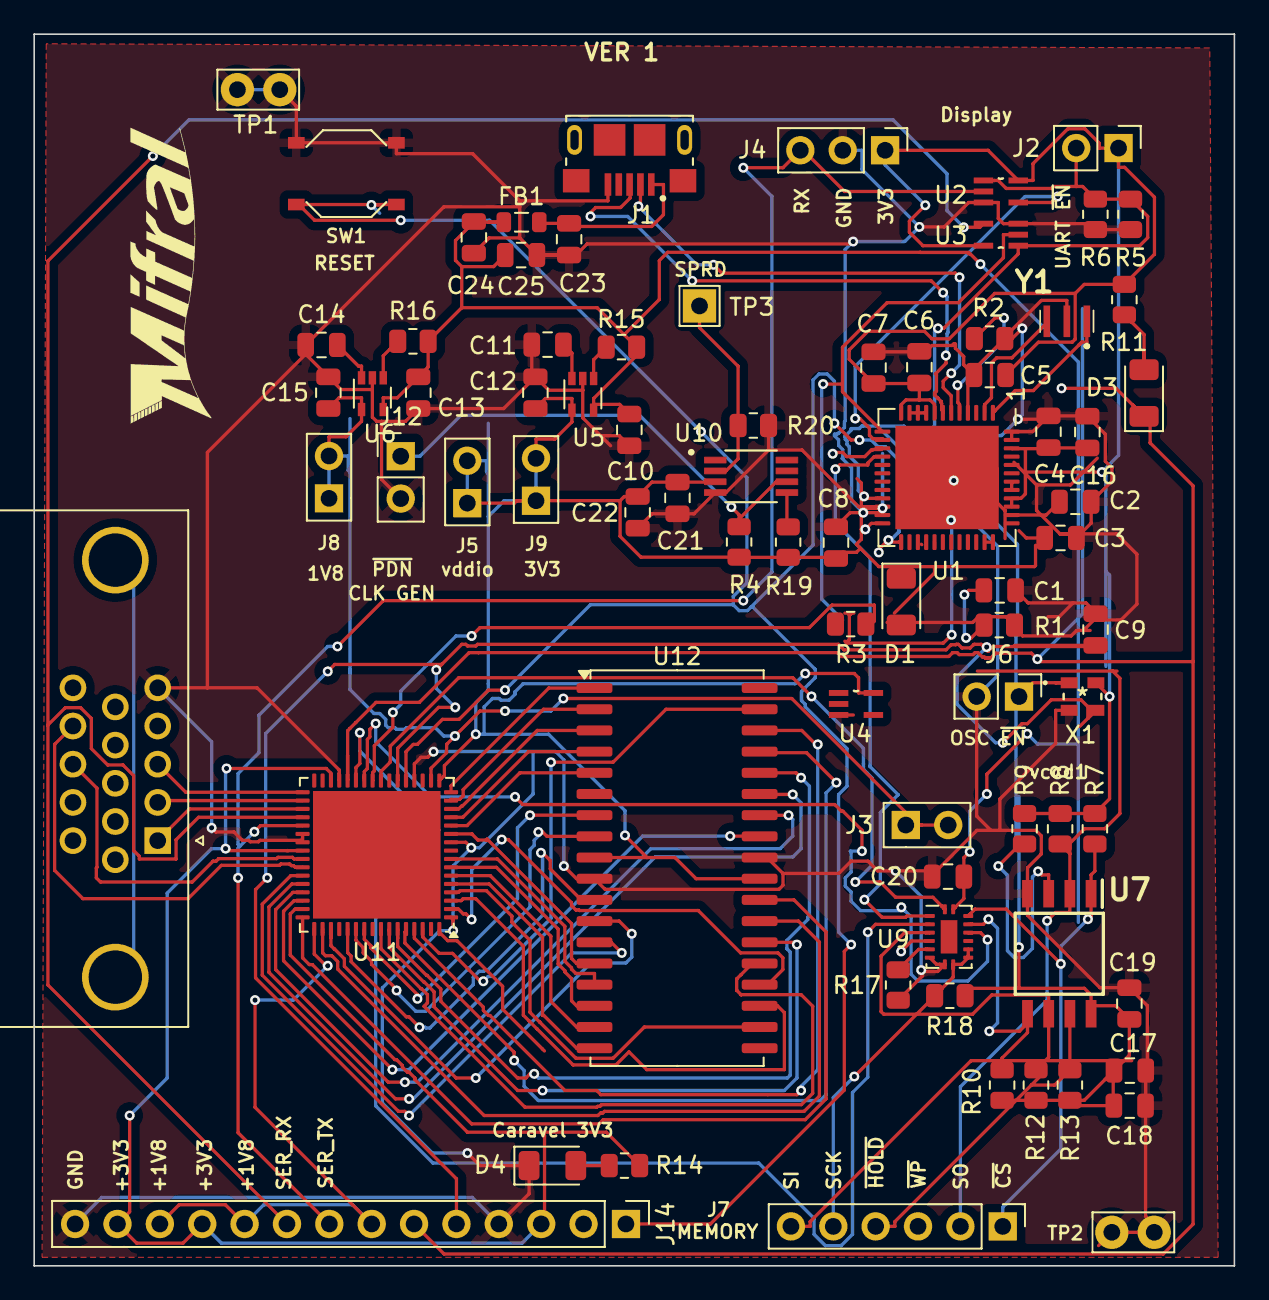
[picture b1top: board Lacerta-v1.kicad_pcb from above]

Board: 2 copper layers, 72.0 x 73.8 mm, 78 parts (0 on the bottom side), 82 nets.

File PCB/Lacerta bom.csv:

Reference,Qty,Value,DNP,price/unit,sum,Vendor,Footprint,Datasheet
"C1,C11,C14,C17,C22,C23",6,0.01uF,CL21B103KBANNNC,0.1,0.6,https://www.digikey.com/en/products/detail/samsung-electro-m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,Capacitor_SMD:C_0805_2012Metric,~
"C2,C3,C4,C5,C6,C7,C8,C9,C18,C20,C21,C24",12,0.1uF,CL21B104KBCNNNC,0.1,1.2,https://www.digikey.com/en/products/detail/samsung-electro-m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,Capacitor_SMD:C_0805_2012Metric,~
"C10,C13,C19",3,1uF,CL05A105KO5NNNC,0.1,0.3,https://www.digikey.com/en/products/detail/samsung-electro-m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,Capacitor_SMD:C_0805_2012Metric,~
"C12,C15,C16,C25",4,10uF,CL21A106KPFNNNE,0.1,0.4,https://www.digikey.com/en/products/detail/samsung-electro-m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,Capacitor_SMD:C_0805_2012Metric,~
"D1,D3,D4",3,RED,LTST-C150KRKT,0.16,0.48,https://www.digikey.com.mx/es/products/detail/liteon/LTST-C1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,LED_SMD:LED_1206_3216Metric,~
FB1,1,600R/0.5A,BMC-Q1JY0600H,0.299,0.299,https://www.mouser.mx/ProductDetail/TE-Connectivity-Sigma-In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,Inductor_SMD:L_0805_2012Metric,~
J1,1,USB_B_Micro,105017-0001,0.92,0.92,https://www.digikey.com.mx/es/products/detail/molex/10501700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,strive_foot_prints:FCI_10118193-0001LF,~
"J2,J6,J12",3,Conn_01x02_Pin,M50-3530242,0.1,0.3,https://www.digikey.com.mx/es/products/detail/harwin-inc/M50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,Connector_PinHeader_2.54mm:PinHeader_1x02_P2.54mm_Vertical,~
"J3,J5,J8,J9",4,Conn_01x02_Pin,M50-3530242,0.1,0.4,https://www.digikey.com.mx/es/products/detail/harwin-inc/M50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,Caravel_Board:Shorted_PinHeader_1x02_P2.54mm_Vertical,~
J4,1,Conn_01x03_Pin,61300311121,0.13,0.13,https://www.digikey.com.mx/es/products/detail/w%C3%BCrth-ele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,Connector_PinHeader_2.54mm:PinHeader_1x03_P2.54mm_Vertical,~
J7,1,Conn_01x06_Pin,61300611121,0.35,0.35,https://www.digikey.com.mx/es/products/detail/w%C3%BCrth-ele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,Connector_PinHeader_2.54mm:PinHeader_1x06_P2.54mm_Vertical,~
J10,1,Conn_01x14_Socket,PPTC141LFBN-RC,0.77,0.77,https://www.digikey.com/en/products/detail/sullins-connector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,Connector_PinSocket_1.00mm:PinSocket_1x14_P1.00mm_Vertical,~
J11,1,Conn_01x10_Pin,61301011121,0.95,0.95,https://www.digikey.com/es/products/detail/w%C3%BCrth-elektr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,Connector_PinHeader_2.54mm:PinHeader_1x10_P2.54mm_Vertical,~
J14,1,Conn_01x15_Pin,PH1-15-UA,0.22,0.22,https://www.digikey.com/es/products/detail/adam-tech/PH1-15-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,Connector_PinHeader_2.54mm:PinHeader_1x15_P2.54mm_Vertical,~
"R1,R4,R7,R8,R9,R10,R12,R13,R15,R16,R17,R18,R19,R20",14,10K,RV0805JR-0710KL,0.13,1.82,https://www.mouser.mx/ProductDetail/YAGEO/RV0805JR-0710KL?qs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,Resistor_SMD:R_0805_2012Metric,~
R2,1,12K 1%,RC0402FR-0712KL,0.1,0.1,https://www.digikey.com/en/products/detail/yageo/RC0402FR-07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,Resistor_SMD:R_0805_2012Metric,~
R3,1,150,RC0402FR-07150RL,0.1,0.1,https://www.digikey.com/en/products/detail/yageo/RC0402FR-07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,Resistor_SMD:R_0805_2012Metric,~
"R5,R6,R11,R14",4,1K,RC0402FR-071KL,0.1,0.4,https://www.digikey.com/es/products/detail/yageo/RC0402FR-07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,Resistor_SMD:R_0805_2012Metric,~
SW1,1,SW_Push - SKQGADE010,SKQGADE010,0.31,0.31,https://www.digikey.com/en/products/detail/alps-alpine/SKQGA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,strive_foot_prints:SW4-SMD-5.2X5.2X1.5MM,~
"TP1,TP2",2,TestPoint,,,,,TestPoint:TestPoint_Bridge_Pitch2.54mm_Drill1.0mm,~
TP3,1,TestPoint,,,,,TestPoint:TestPoint_THTPad_2.0x2.0mm_Drill1.0mm,~
U1,1,FT232H,FT232HQ,4.09,4.09,https://www.digikey.com.mx/es/products/detail/ftdi-future-te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,Package_DFN_QFN:QFN-48-1EP_8x8mm_P0.5mm_EP6.2x6.2mm,http://www.ftdichip.com/Products/ICs/FT232H.htm
"U2,U3,U4",3,SN74LVC1G125DCKR,SN74LVC1G125DCKR,0.1,0.3,https://www.digikey.com/en/products/detail/texas-instruments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,strive_foot_prints:SOT65P210X110-5N,SC-70-5
"U5,U6",2,TAR5SxxU,TAR5S16U,0.49,0.98,https://www.digikey.com/en/products/detail/toshiba-semicondu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,Caravel_Board:SOT-353F,https://toshiba.semicon-storage.com/info/TAR5S16U_datasheet_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
U7,1,W25Q32FVSS,W25Q32JVSSIQ,0.93,0.93,https://www.digikey.com/es/products/detail/winbond-electroni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,strive_foot_prints:SOIC127P790X216-8N,
U9,1,TMUX4053-BQB,TMUX4053PWR,0.58,0.58,https://www.digikey.com/en/products/detail/texas-instruments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,Caravel_Board:WQFN-16-1EP_2.5x3.5mm_P0.5mm_EP1x2mm,https://www.ti.com/lit/ds/symlink/tmux4051.pdf?ts=1695248347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
U10,1,DS1086LU,DS1086LU+T,4.47,4.47,https://www.digikey.com/en/products/detail/analog-devices-in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,Caravel_Board:SOP65P490X110-8N,https://www.analog.com/media/en/technical-documentation/data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
U11,1,Caravel_QFN,chip,,0,,Package_DFN_QFN:QFN-64-1EP_9x9mm_P0.5mm_EP7.65x7.65mm,
U12,1,CY7C1049GN-10VXI,CY7C1049GN-10VXI,5.72,5.72,https://www.digikey.com/en/products/detail/infineon-technolo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,Package_SO:SOJ-36_10.16x23.495mm_P1.27mm,http://www.issi.com/WW/pdf/61-64C5128AL.pdf
X1,1,DSC6001_10MHZ,DSC6001JE1B-010.0000,0.59,0.59,https://www.digikey.com/en/products/detail/microchip-technol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,strive_foot_prints:DSC6001JE1A-010.0000,http://cdn-reichelt.de/documents/datenblatt/B400/XO91.pdf
Y1,1,12MHz,ABM8-272-T3,0.54,0.54,https://www.digikey.com/en/products/detail/abracon-llc/ABM8-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,strive_foot_prints:CSTNE12M0GH5L000R0,~
,,,,Total,28.459,,,

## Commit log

2026-03-26 Revise README with project details and updates
    Updated project overview, added graphical components, and clarified GPIO configuration details.
2026-03-26 Deployed 6c5e75b with MkDocs version: 1.6.1
2026-03-26 first push test
2026-03-26 readme, VGA & UART
2026-03-26 link onreadme
2026-03-26 GUI development files added
2026-03-26 Deployed dec5923 with MkDocs version: 1.6.1
2026-03-26 README improvment
2026-03-26 PCB folder added
2026-03-26 layout readme section
2026-04-18 Deployed e350ef0 with MkDocs version: 1.6.1
2026-04-30 Deployed e350ef0 with MkDocs version: 1.5.3
2026-05-01 Update ChipFoundry submission with compressed wrapper files
2026-05-01 project.json update
2026-05-01 chipfoundry: remote precheck results (69c0a0ab-8ea1-44f1-b2eb-6c2ff12d29f3)
2026-05-01 chipfoundry: remote precheck results (a765991d-a97d-4311-84f0-c38c2d0cbb17)
2026-05-01 readme introduction
2026-05-01 readme introductionv2
2026-05-01 Update submission without large uncompressed files
2026-05-01 Deployed e86949f with MkDocs version: 1.5.3
2026-05-01 chipfoundry: remote precheck results (bf529bb2-ff98-4276-bdfe-9ef53bd91e87)
2026-05-01 Ignore large precheck GDS outputs 2
2026-05-01 Update README with precheck log and PCB information
    Added precheck log details and updated PCB description.
2026-05-01 chipfoundry: remote precheck results (01ac86ab-a619-4f4b-ac1d-18d7b12c89c8)
2026-05-01 chipfoundry: remote precheck results (e3d78221-a77e-4c1b-b264-ece87f719e7d)
2026-05-07 final release
2026-05-26 chipfoundry: remote precheck results (0dd8e2ad-8756-49f3-bf5d-44229e4bc1b0)

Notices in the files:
parts and their libraries:
Copyright 2016 Accelerated Designs. All rights reserved.
